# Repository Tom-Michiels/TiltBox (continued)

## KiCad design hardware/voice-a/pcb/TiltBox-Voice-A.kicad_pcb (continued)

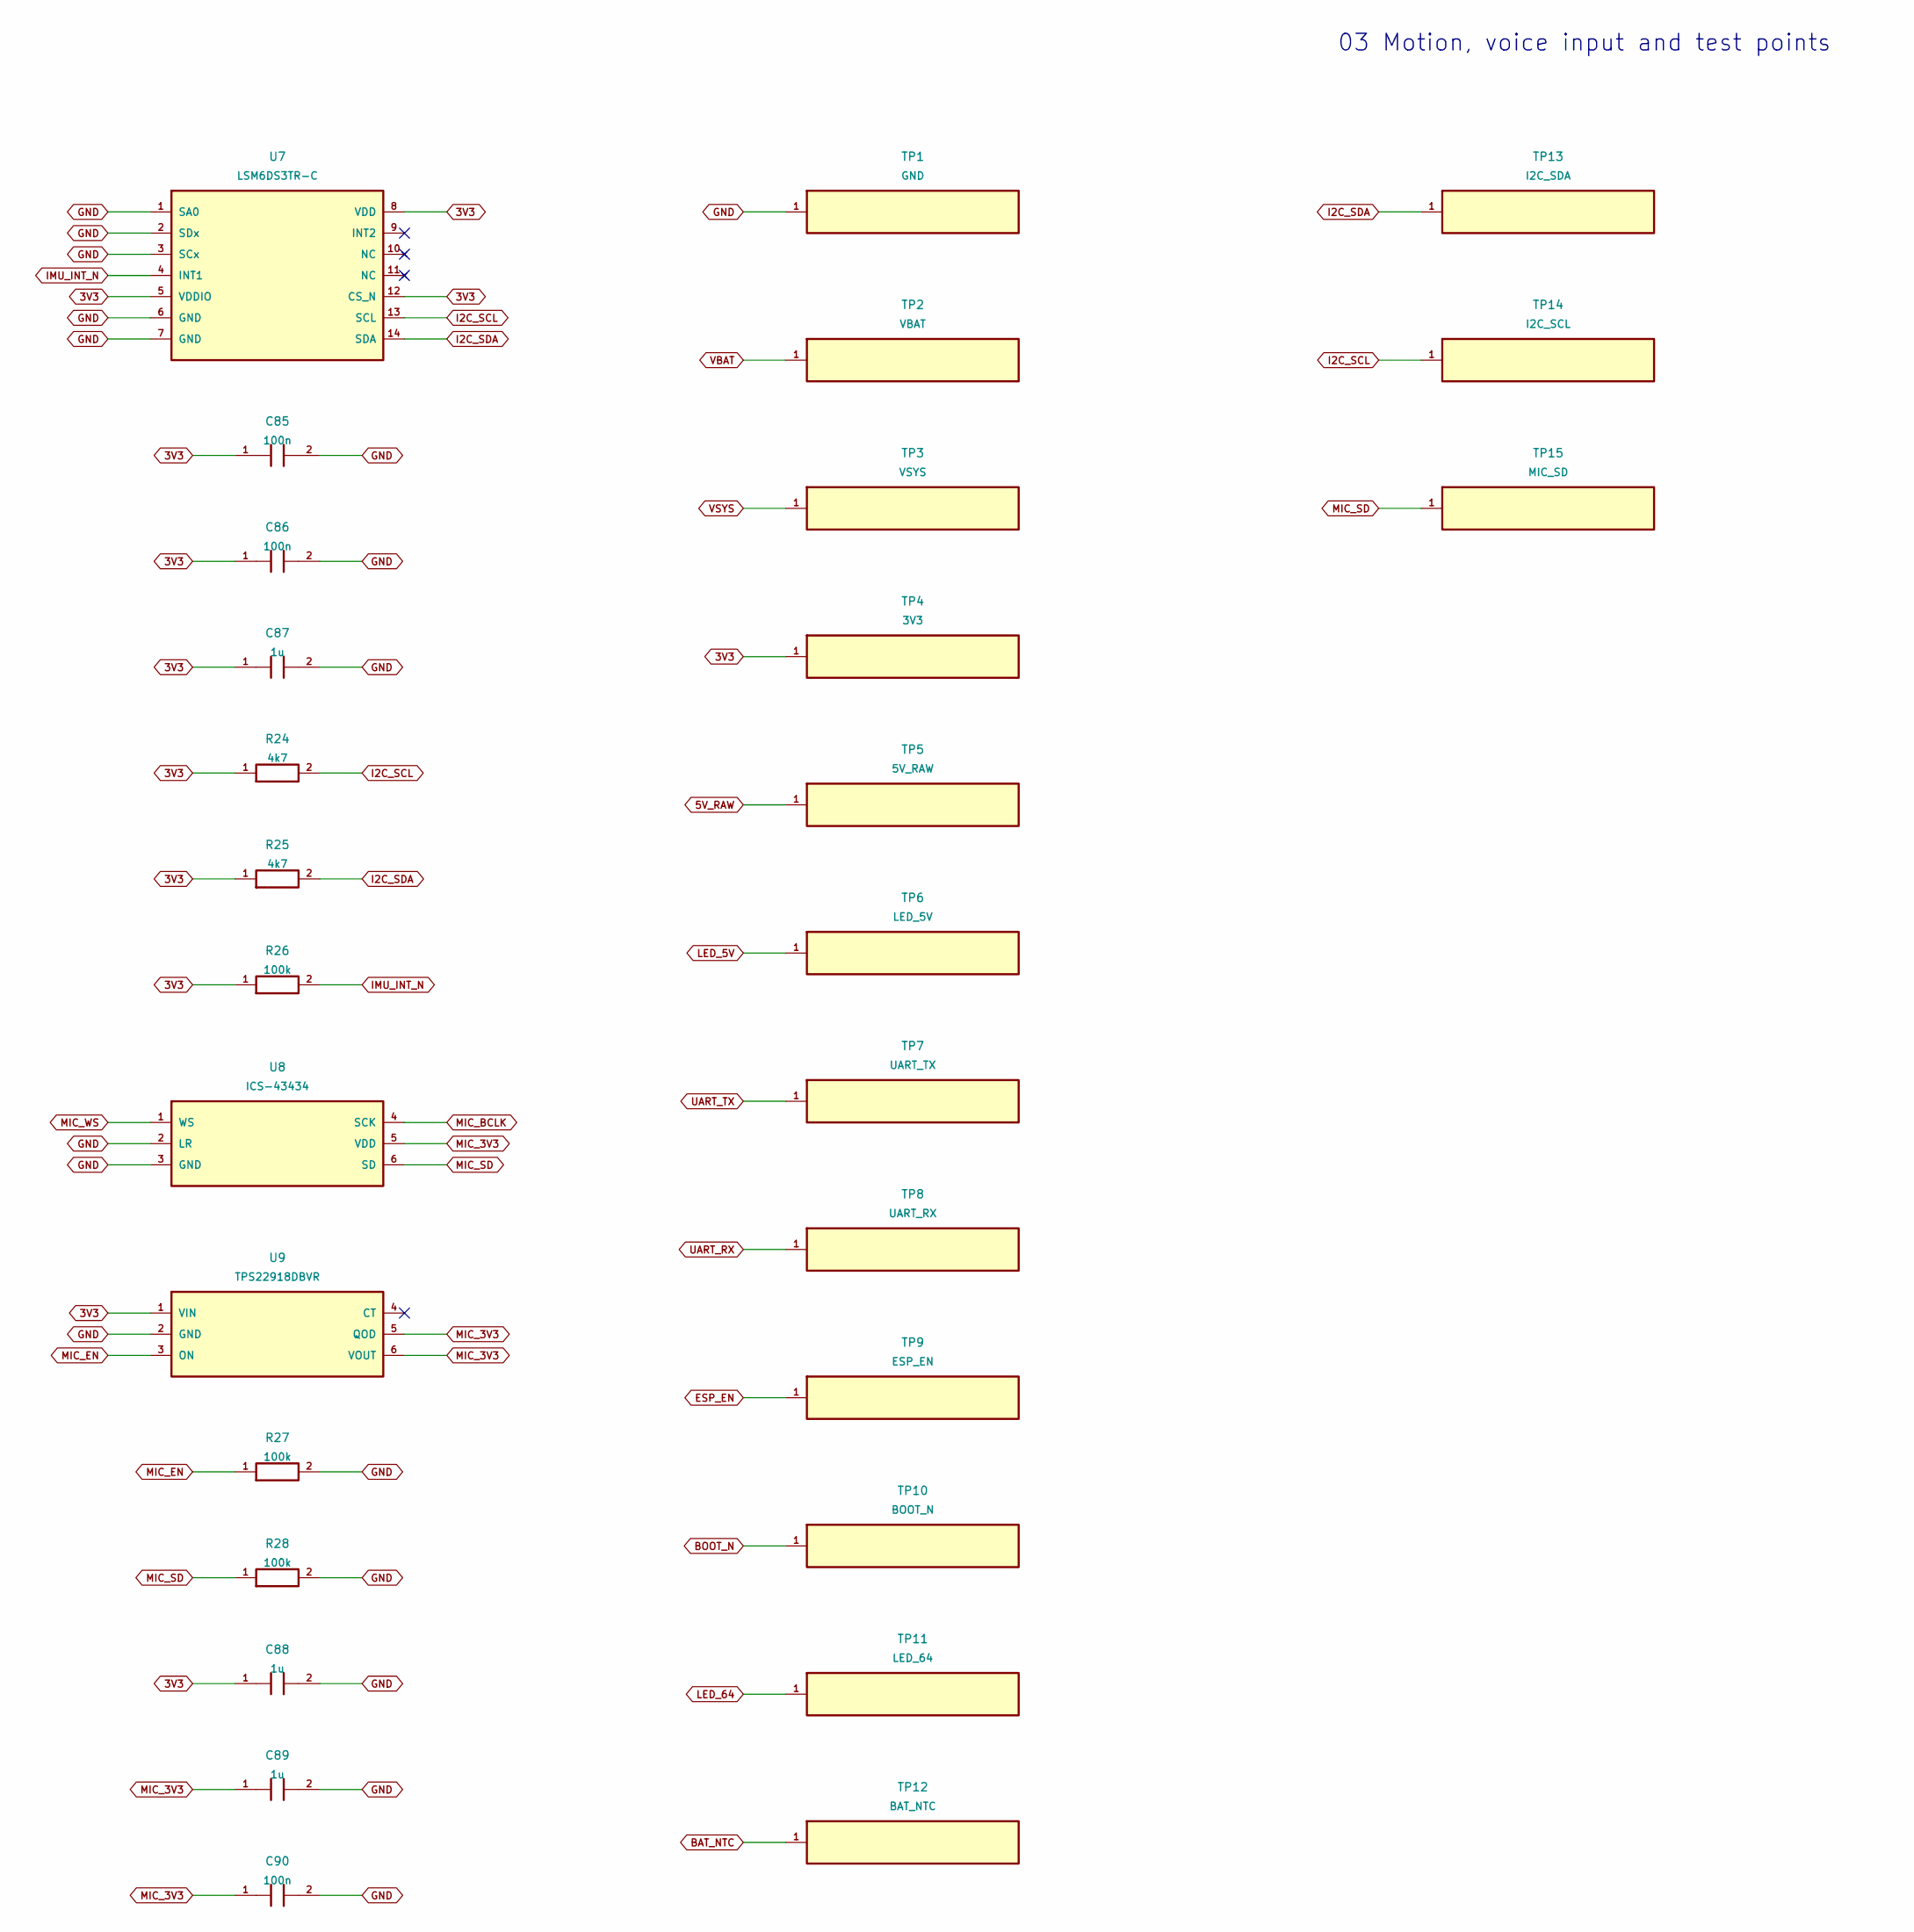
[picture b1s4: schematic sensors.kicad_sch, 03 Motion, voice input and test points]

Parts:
C85, C86, C90: 100n; C_0402_1005Metric; LCSC Part C1525
C87, C88, C89: 1u; C_0603_1608Metric; LCSC Part C15849
R24, R25: 4k7; R_0402_1005Metric; LCSC Part C25900
R26, R27, R28: 100k; R_0402_1005Metric; LCSC Part C25741
TP1: GND; TestPoint_Pad_D1.5mm
TP2: VBAT; TestPoint_Pad_D1.5mm
TP3: VSYS; TestPoint_Pad_D1.5mm
TP4: 3V3; TestPoint_Pad_D1.5mm
TP5: 5V_RAW; TestPoint_Pad_D1.5mm
TP6: LED_5V; TestPoint_Pad_D1.5mm
TP7: UART_TX; TestPoint_Pad_D1.5mm
TP8: UART_RX; TestPoint_Pad_D1.5mm
TP9: ESP_EN; TestPoint_Pad_D1.5mm
TP10: BOOT_N; TestPoint_Pad_D1.5mm
TP11: LED_64; TestPoint_Pad_D1.5mm
TP12: BAT_NTC; TestPoint_Pad_D1.5mm
TP13: I2C_SDA; TestPoint_Pad_D1.5mm
TP14: I2C_SCL; TestPoint_Pad_D1.5mm
TP15: MIC_SD; TestPoint_Pad_D1.5mm
U7: LSM6DS3TR-C; LGA-14_3x2.5mm_P0.5mm_LayoutBorder3x4y; LCSC Part C967633
U8: ICS-43434; InvenSense_ICS-43434-6_3.5x2.65mm; LCSC Part C5656610
U9: TPS22918DBVR; SOT-23-6; LCSC Part C131941

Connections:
3V3: C85.1, C86.1, C87.1, C88.1, R24.1, R25.1, R26.1, TP4.1, U7.5 (VDDIO), U7.8 (VDD), U7.12 (CS_N), U9.1 (VIN); also elsewhere on the board
5V_RAW: TP5.1; also elsewhere on the board
BAT_NTC: TP12.1; also elsewhere on the board
BOOT_N: TP10.1; also elsewhere on the board
ESP_EN: TP9.1; also elsewhere on the board
GND: C85.2, C86.2, C87.2, C88.2, C89.2, C90.2, R27.2, R28.2, TP1.1, U7.1 (SA0), U7.2 (SDx), U7.3 (SCx), U7.6 (GND), U7.7 (GND), U8.2 (LR), U8.3 (GND), U9.2 (GND); also elsewhere on the board
I2C_SCL: R24.2, TP14.1, U7.13 (SCL); also elsewhere on the board
I2C_SDA: R25.2, TP13.1, U7.14 (SDA); also elsewhere on the board
IMU_INT_N: R26.2, U7.4 (INT1); also elsewhere on the board
LED_5V: TP6.1; also elsewhere on the board
LED_64: TP11.1; also elsewhere on the board
MIC_3V3: C89.1, C90.1, U8.5 (VDD), U9.5 (QOD), U9.6 (VOUT)
MIC_BCLK: U8.4 (SCK); also elsewhere on the board
MIC_EN: R27.1, U9.3 (ON); also elsewhere on the board
MIC_SD: R28.1, TP15.1, U8.6 (SD); also elsewhere on the board
MIC_WS: U8.1 (WS); also elsewhere on the board
UART_RX: TP8.1; also elsewhere on the board
UART_TX: TP7.1; also elsewhere on the board
VBAT: TP2.1; also elsewhere on the board
VSYS: TP3.1; also elsewhere on the board

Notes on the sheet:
03 Motion, voice input and test points

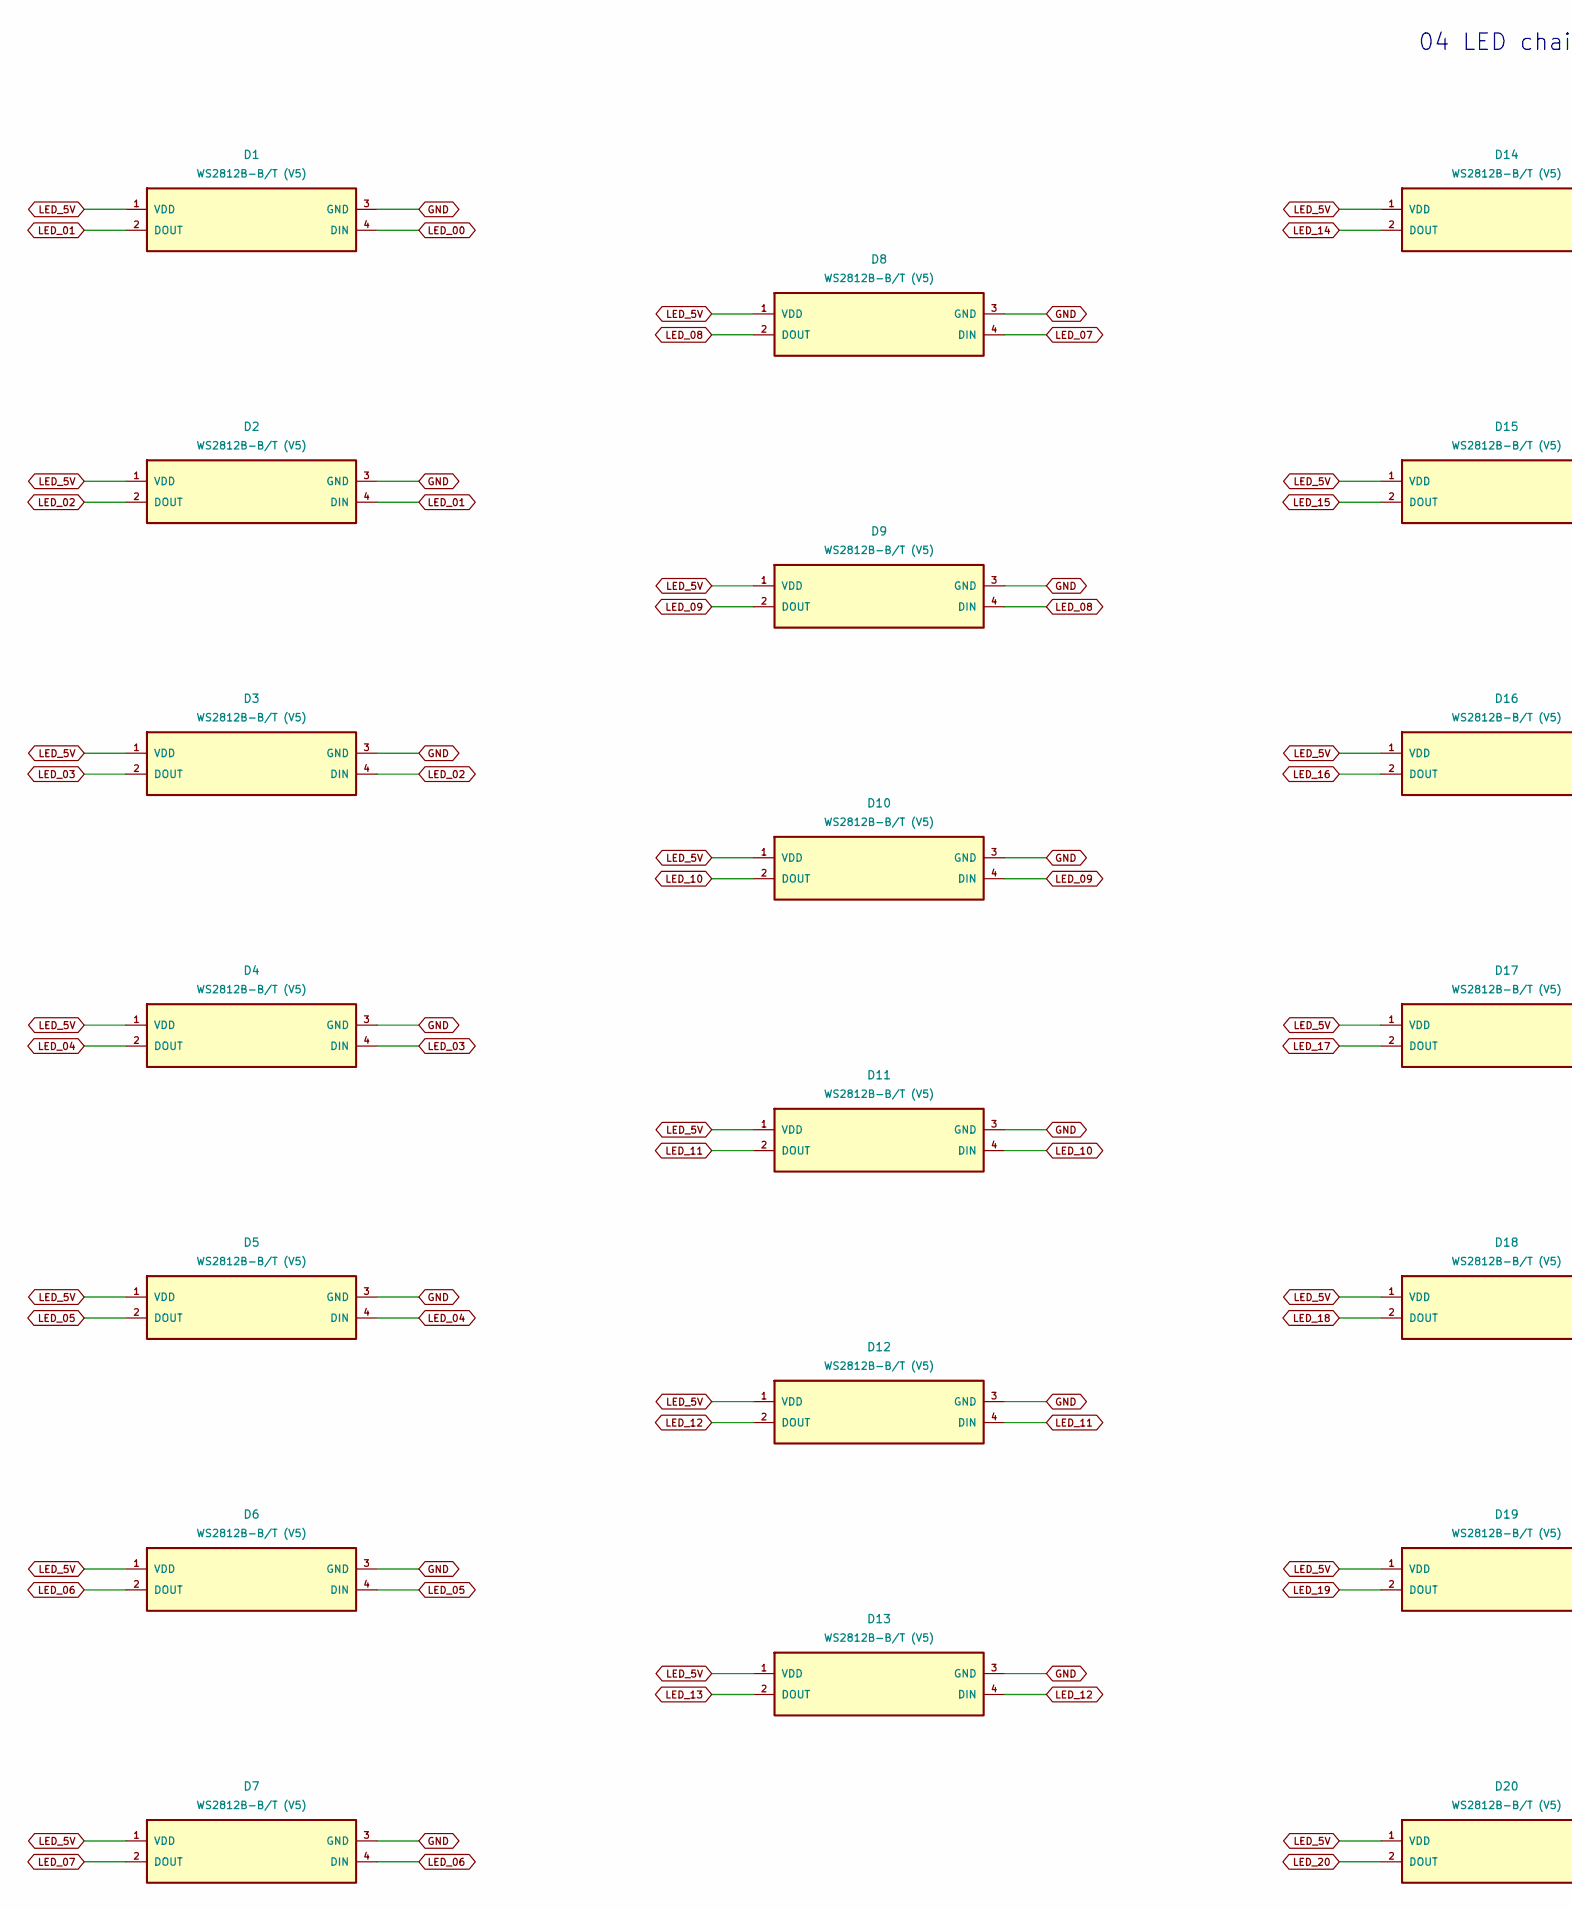
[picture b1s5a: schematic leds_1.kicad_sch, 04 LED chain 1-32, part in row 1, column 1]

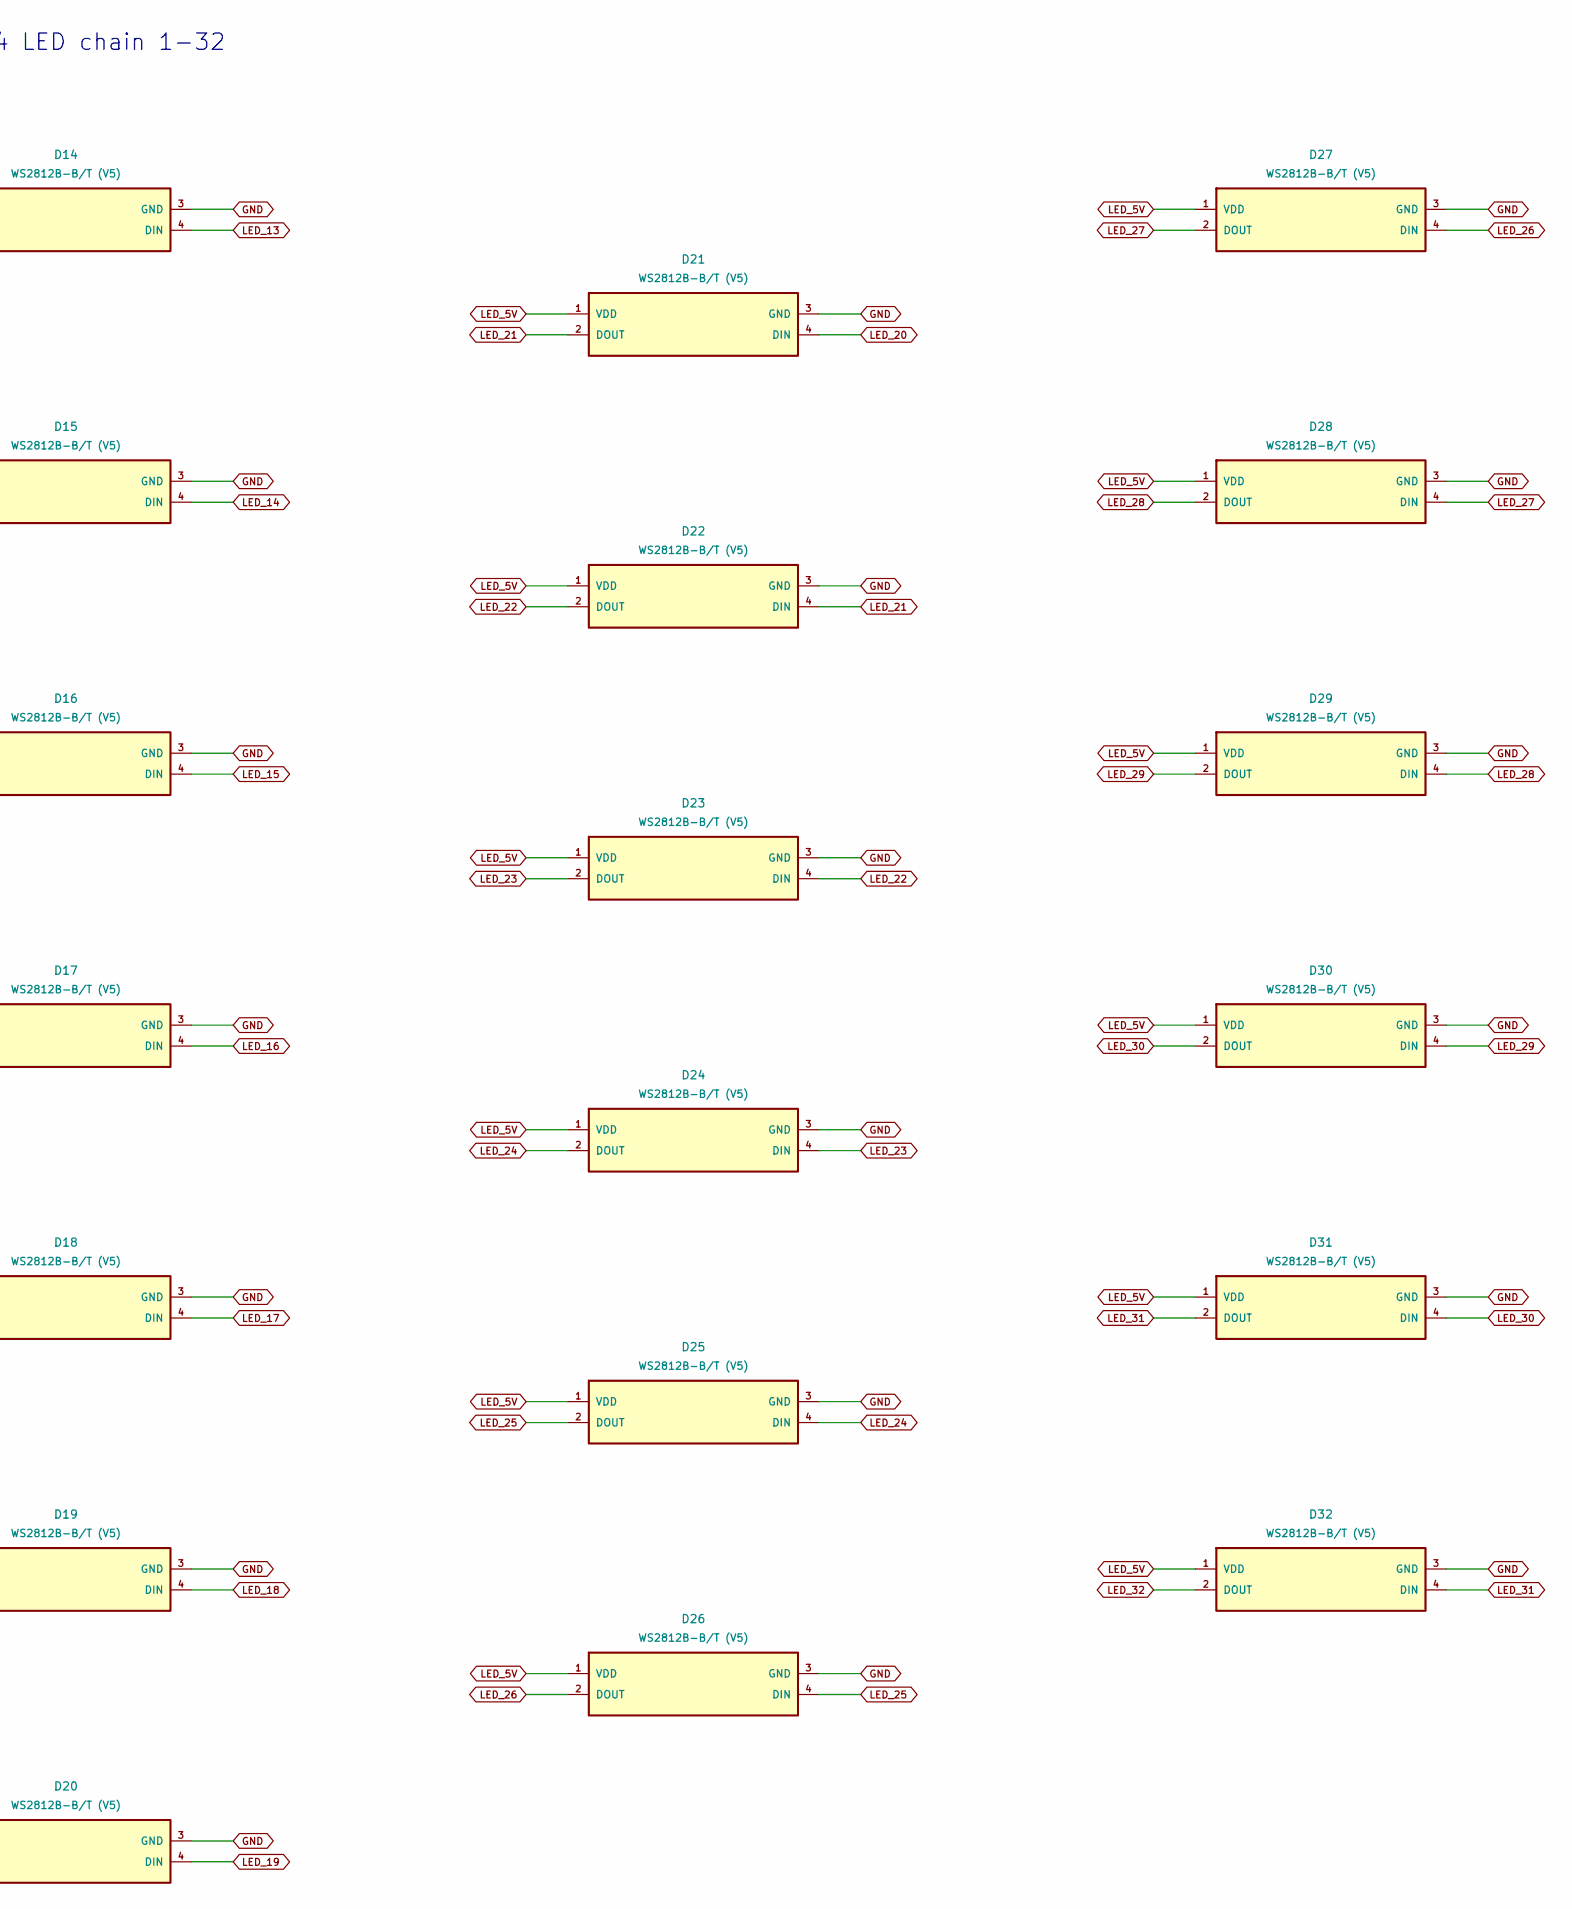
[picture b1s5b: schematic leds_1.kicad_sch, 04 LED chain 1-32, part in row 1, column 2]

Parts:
D1, D2, D3, D4, D5, D6, D7, D8, D9, D10, D11, D12, D13, D14, D15, D16, D17, D18, D19, D20, D21, D22, D23, D24, D25, D26, D27, D28, D29, D30, D31, D32: WS2812B-B/T (V5); LED_WS2812B_PLCC4_5.0x5.0mm_P3.2mm; LCSC Part C2761795

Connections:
GND: D1.3 (GND), D2.3 (GND), D3.3 (GND), D4.3 (GND), D5.3 (GND), D6.3 (GND), D7.3 (GND), D8.3 (GND), D9.3 (GND), D10.3 (GND), D11.3 (GND), D12.3 (GND), D13.3 (GND), D14.3 (GND), D15.3 (GND), D16.3 (GND), D17.3 (GND), D18.3 (GND), D19.3 (GND), D20.3 (GND), D21.3 (GND), D22.3 (GND), D23.3 (GND), D24.3 (GND), D25.3 (GND), D26.3 (GND), D27.3 (GND), D28.3 (GND), D29.3 (GND), D30.3 (GND), D31.3 (GND), D32.3 (GND); also elsewhere on the board
LED_00: D1.4 (DIN); also elsewhere on the board
LED_01: D1.2 (DOUT), D2.4 (DIN)
LED_02: D2.2 (DOUT), D3.4 (DIN)
LED_03: D3.2 (DOUT), D4.4 (DIN)
LED_04: D4.2 (DOUT), D5.4 (DIN)
LED_05: D5.2 (DOUT), D6.4 (DIN)
LED_5V: D1.1 (VDD), D2.1 (VDD), D3.1 (VDD), D4.1 (VDD), D5.1 (VDD), D6.1 (VDD), D7.1 (VDD), D8.1 (VDD), D9.1 (VDD), D10.1 (VDD), D11.1 (VDD), D12.1 (VDD), D13.1 (VDD), D14.1 (VDD), D15.1 (VDD), D16.1 (VDD), D17.1 (VDD), D18.1 (VDD), D19.1 (VDD), D20.1 (VDD), D21.1 (VDD), D22.1 (VDD), D23.1 (VDD), D24.1 (VDD), D25.1 (VDD), D26.1 (VDD), D27.1 (VDD), D28.1 (VDD), D29.1 (VDD), D30.1 (VDD), D31.1 (VDD), D32.1 (VDD); also elsewhere on the board
LED_06: D6.2 (DOUT), D7.4 (DIN)
LED_07: D7.2 (DOUT), D8.4 (DIN)
LED_08: D8.2 (DOUT), D9.4 (DIN)
LED_09: D9.2 (DOUT), D10.4 (DIN)
LED_10: D10.2 (DOUT), D11.4 (DIN)
LED_11: D11.2 (DOUT), D12.4 (DIN)
LED_12: D12.2 (DOUT), D13.4 (DIN)
LED_13: D13.2 (DOUT), D14.4 (DIN)
LED_14: D14.2 (DOUT), D15.4 (DIN)
LED_15: D15.2 (DOUT), D16.4 (DIN)
LED_16: D16.2 (DOUT), D17.4 (DIN)
LED_17: D17.2 (DOUT), D18.4 (DIN)
LED_18: D18.2 (DOUT), D19.4 (DIN)
LED_19: D19.2 (DOUT), D20.4 (DIN)
LED_20: D20.2 (DOUT), D21.4 (DIN)
LED_21: D21.2 (DOUT), D22.4 (DIN)
LED_22: D22.2 (DOUT), D23.4 (DIN)
LED_23: D23.2 (DOUT), D24.4 (DIN)
LED_24: D24.2 (DOUT), D25.4 (DIN)
LED_25: D25.2 (DOUT), D26.4 (DIN)
LED_26: D26.2 (DOUT), D27.4 (DIN)
LED_27: D27.2 (DOUT), D28.4 (DIN)
LED_28: D28.2 (DOUT), D29.4 (DIN)
LED_29: D29.2 (DOUT), D30.4 (DIN)
LED_30: D30.2 (DOUT), D31.4 (DIN)
LED_31: D31.2 (DOUT), D32.4 (DIN)
LED_32: D32.2 (DOUT); also elsewhere on the board

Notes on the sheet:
04 LED chain 1-32

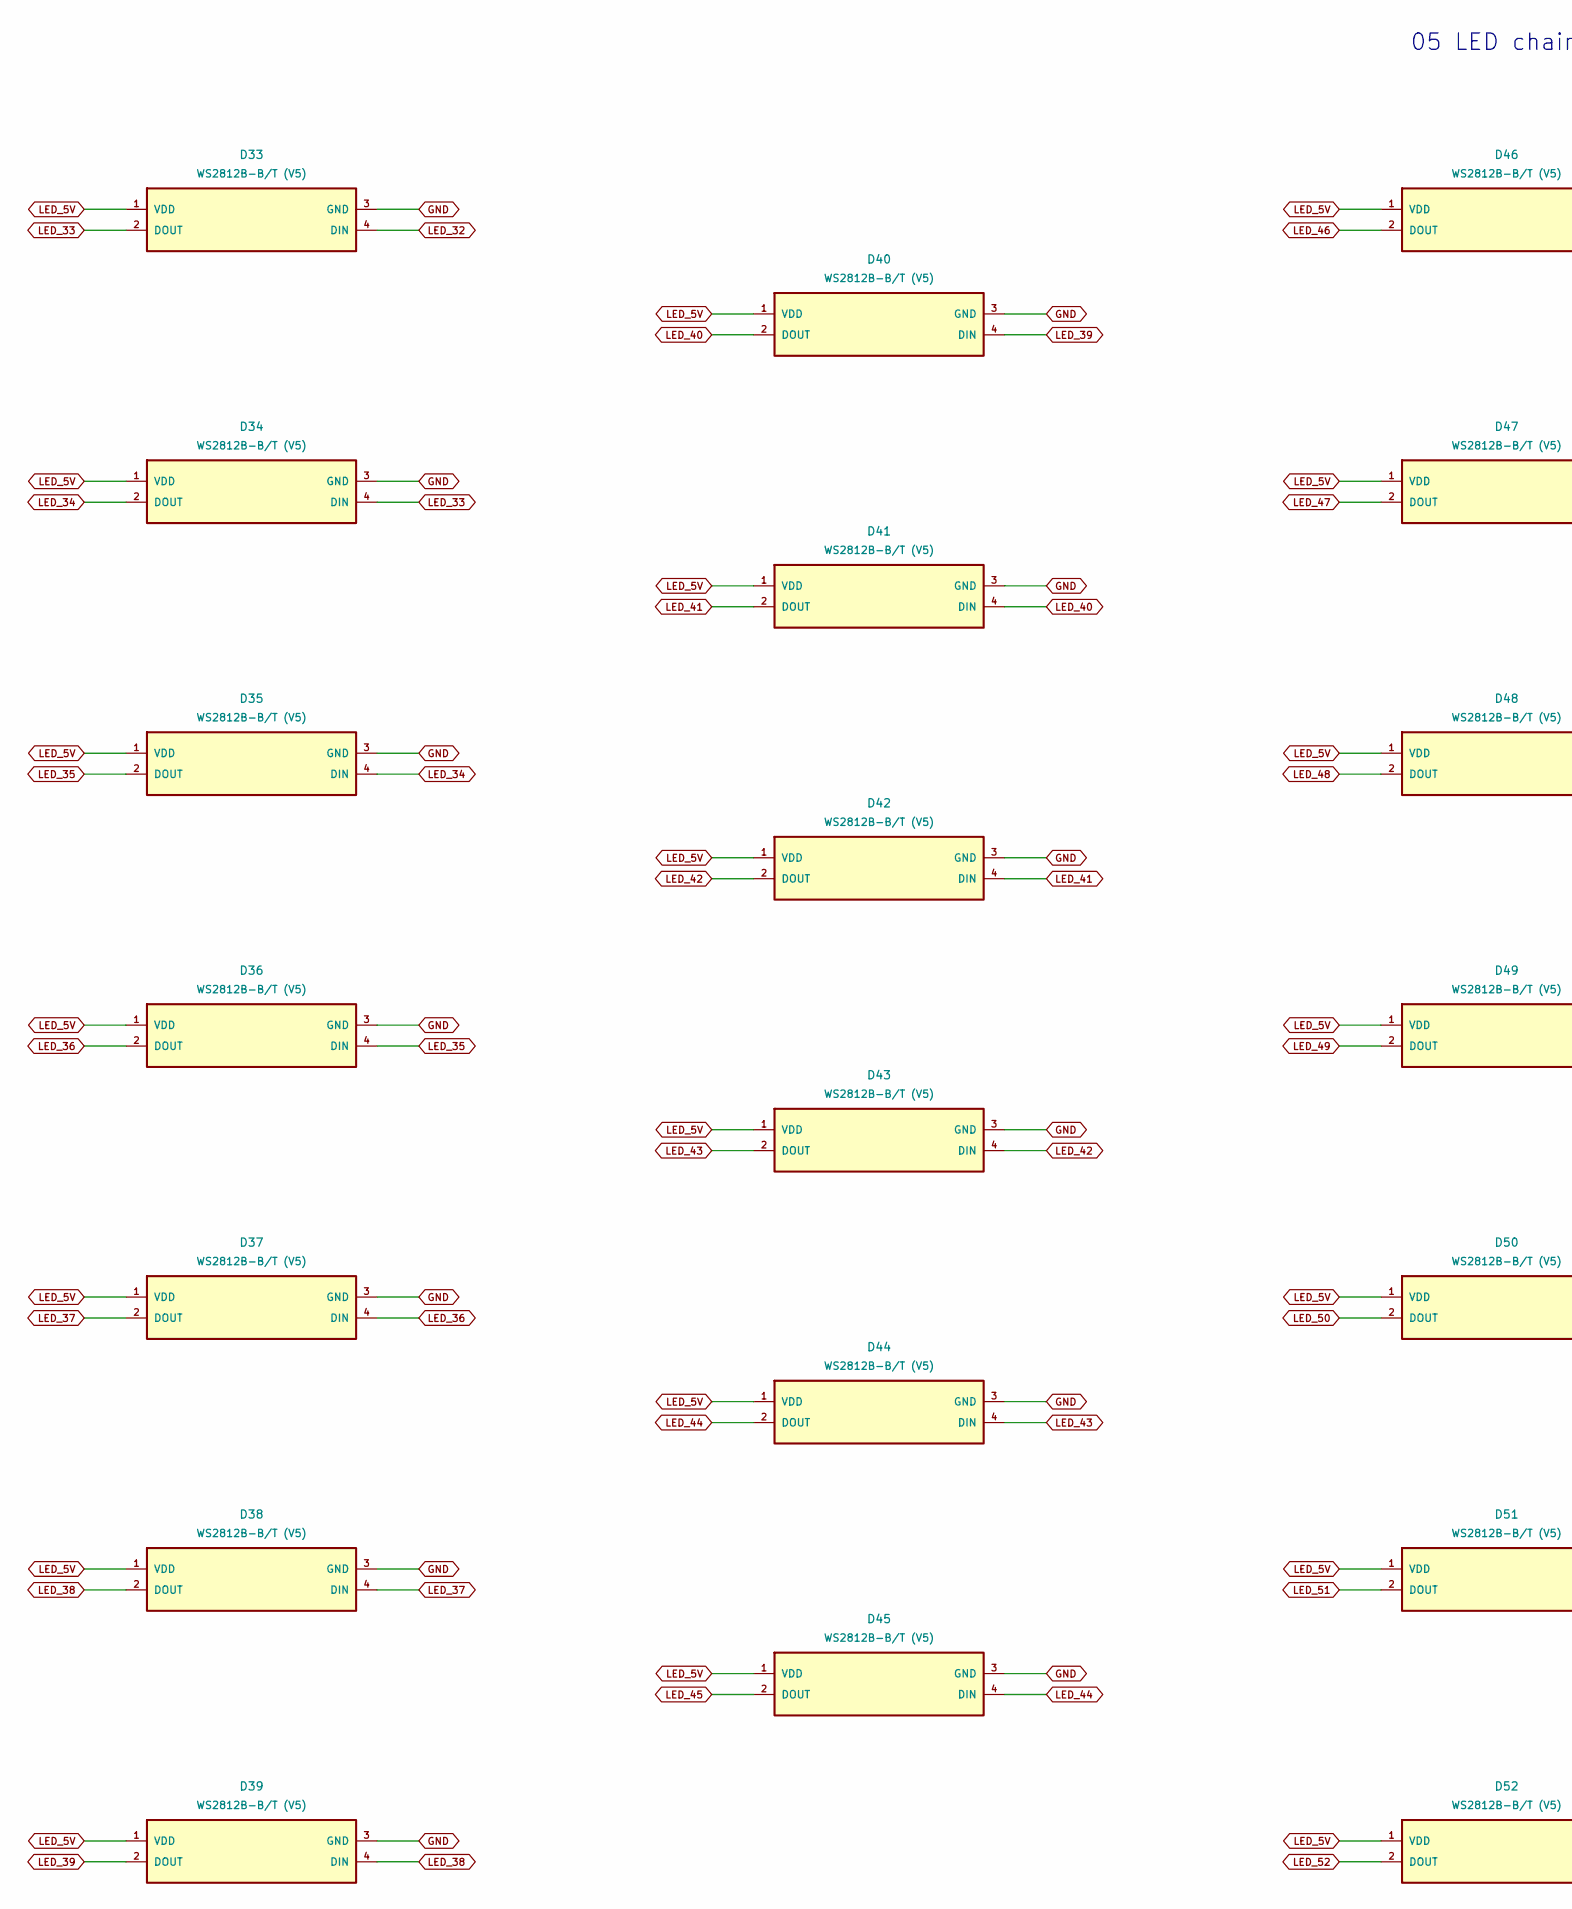
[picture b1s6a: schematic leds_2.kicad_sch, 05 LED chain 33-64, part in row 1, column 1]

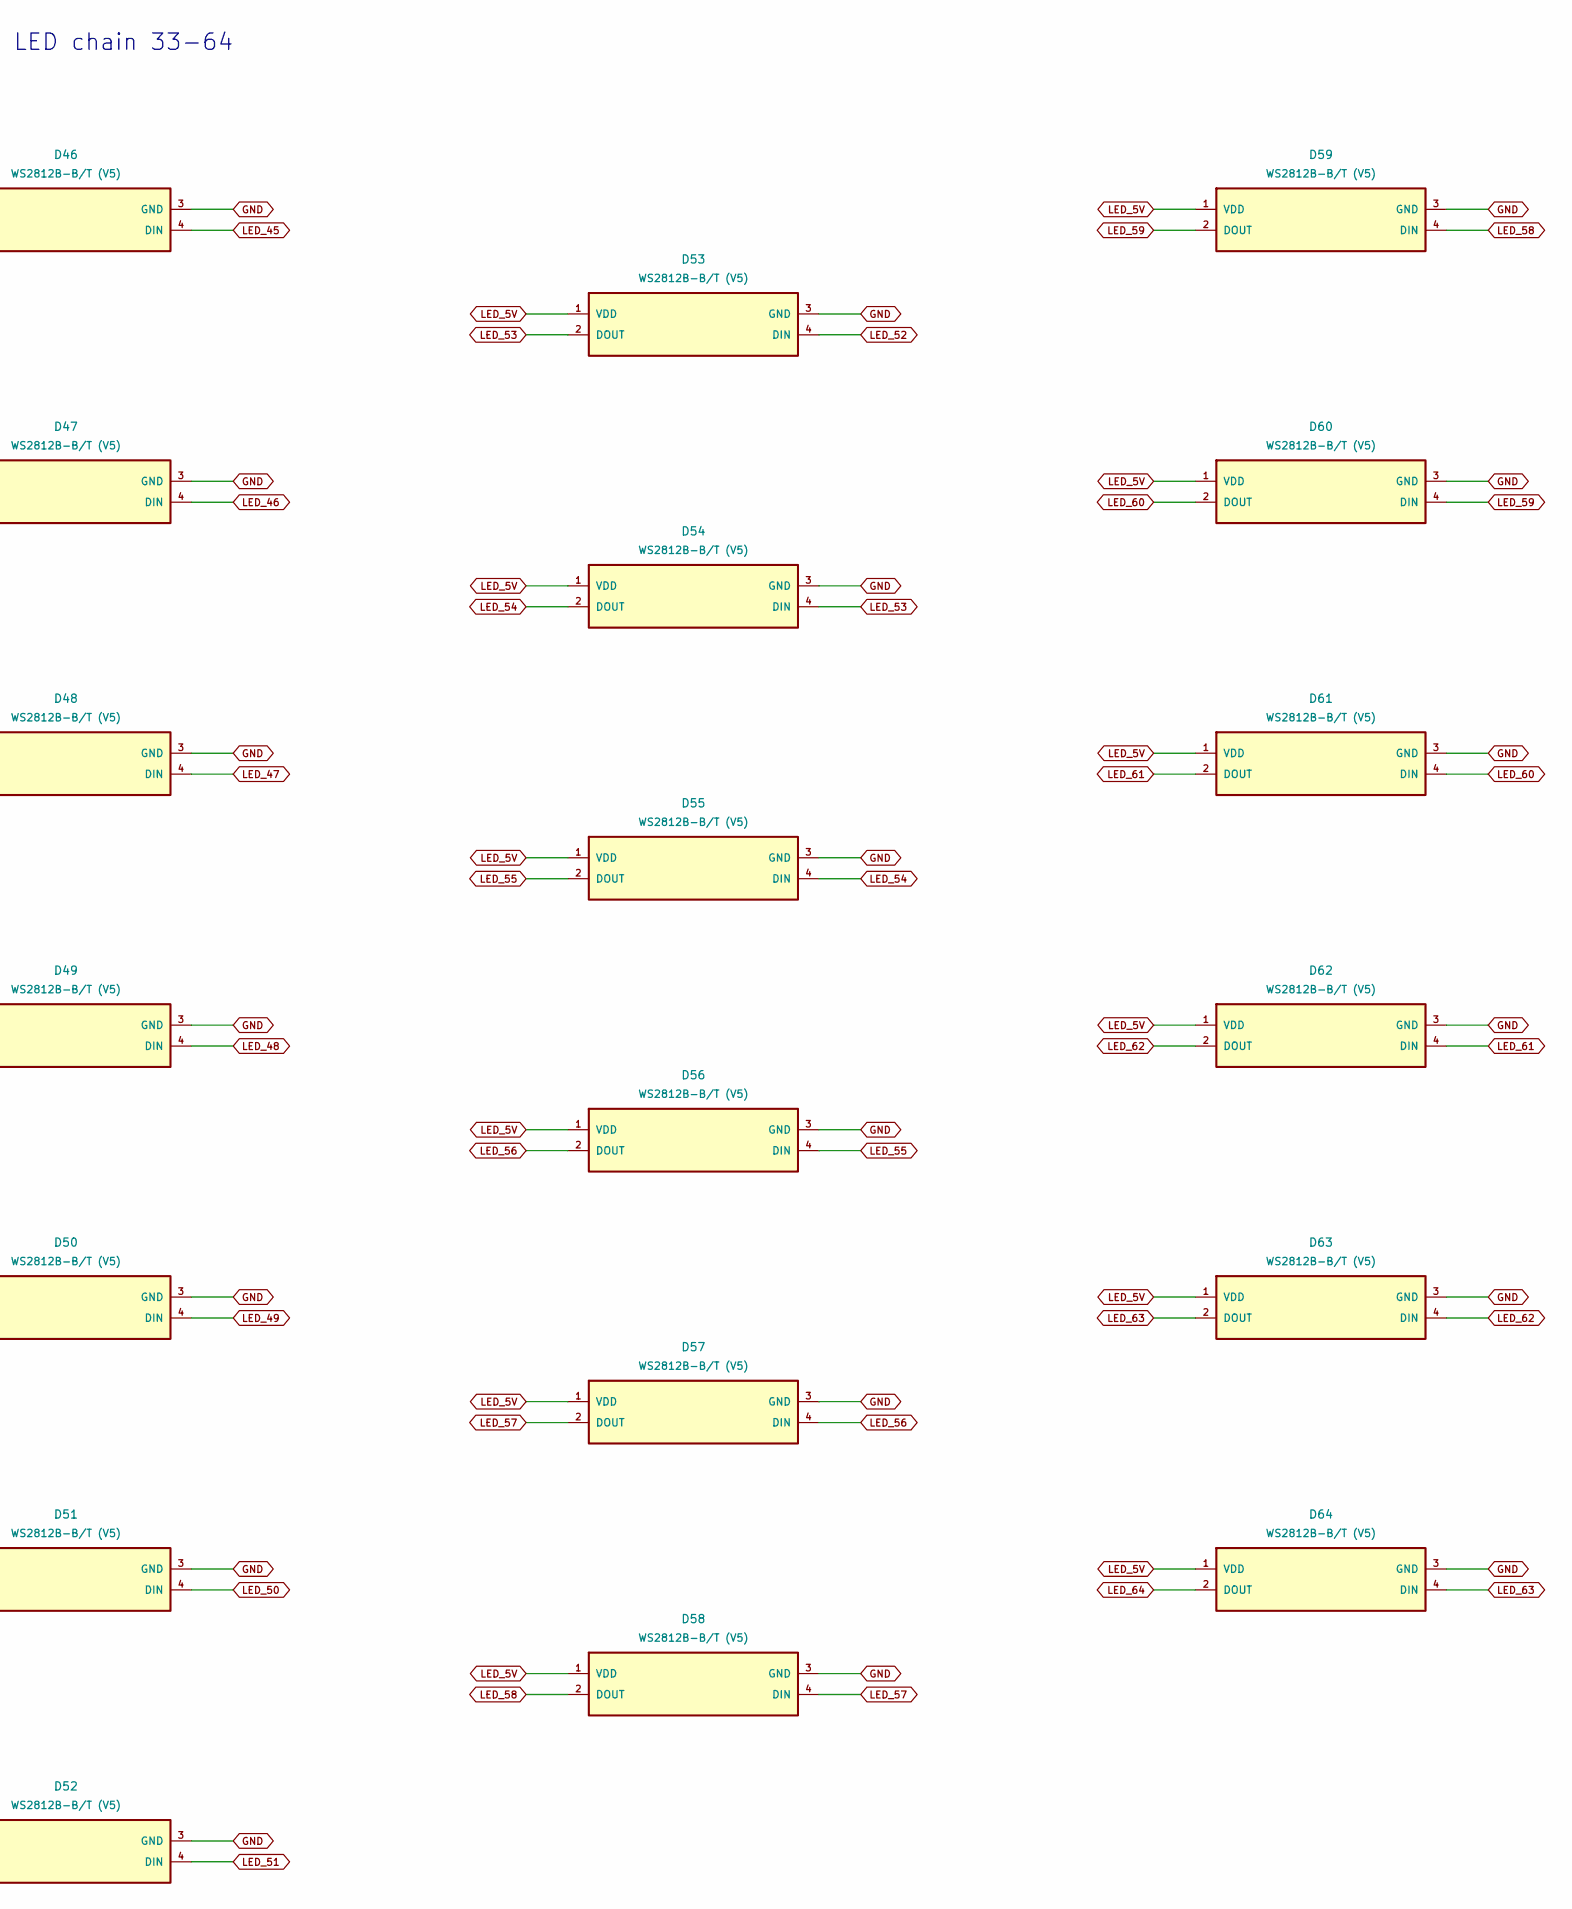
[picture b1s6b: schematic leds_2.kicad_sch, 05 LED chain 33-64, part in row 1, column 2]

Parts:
D33, D34, D35, D36, D37, D38, D39, D40, D41, D42, D43, D44, D45, D46, D47, D48, D49, D50, D51, D52, D53, D54, D55, D56, D57, D58, D59, D60, D61, D62, D63, D64: WS2812B-B/T (V5); LED_WS2812B_PLCC4_5.0x5.0mm_P3.2mm; LCSC Part C2761795

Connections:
GND: D33.3 (GND), D34.3 (GND), D35.3 (GND), D36.3 (GND), D37.3 (GND), D38.3 (GND), D39.3 (GND), D40.3 (GND), D41.3 (GND), D42.3 (GND), D43.3 (GND), D44.3 (GND), D45.3 (GND), D46.3 (GND), D47.3 (GND), D48.3 (GND), D49.3 (GND), D50.3 (GND), D51.3 (GND), D52.3 (GND), D53.3 (GND), D54.3 (GND), D55.3 (GND), D56.3 (GND), D57.3 (GND), D58.3 (GND), D59.3 (GND), D60.3 (GND), D61.3 (GND), D62.3 (GND), D63.3 (GND), D64.3 (GND); also elsewhere on the board
LED_5V: D33.1 (VDD), D34.1 (VDD), D35.1 (VDD), D36.1 (VDD), D37.1 (VDD), D38.1 (VDD), D39.1 (VDD), D40.1 (VDD), D41.1 (VDD), D42.1 (VDD), D43.1 (VDD), D44.1 (VDD), D45.1 (VDD), D46.1 (VDD), D47.1 (VDD), D48.1 (VDD), D49.1 (VDD), D50.1 (VDD), D51.1 (VDD), D52.1 (VDD), D53.1 (VDD), D54.1 (VDD), D55.1 (VDD), D56.1 (VDD), D57.1 (VDD), D58.1 (VDD), D59.1 (VDD), D60.1 (VDD), D61.1 (VDD), D62.1 (VDD), D63.1 (VDD), D64.1 (VDD); also elsewhere on the board
LED_32: D33.4 (DIN); also elsewhere on the board
LED_33: D33.2 (DOUT), D34.4 (DIN)
LED_34: D34.2 (DOUT), D35.4 (DIN)
LED_35: D35.2 (DOUT), D36.4 (DIN)
LED_36: D36.2 (DOUT), D37.4 (DIN)
LED_37: D37.2 (DOUT), D38.4 (DIN)
LED_38: D38.2 (DOUT), D39.4 (DIN)
LED_39: D39.2 (DOUT), D40.4 (DIN)
LED_40: D40.2 (DOUT), D41.4 (DIN)
LED_41: D41.2 (DOUT), D42.4 (DIN)
LED_42: D42.2 (DOUT), D43.4 (DIN)
LED_43: D43.2 (DOUT), D44.4 (DIN)
LED_44: D44.2 (DOUT), D45.4 (DIN)
LED_45: D45.2 (DOUT), D46.4 (DIN)
LED_46: D46.2 (DOUT), D47.4 (DIN)
LED_47: D47.2 (DOUT), D48.4 (DIN)
LED_48: D48.2 (DOUT), D49.4 (DIN)
LED_49: D49.2 (DOUT), D50.4 (DIN)
LED_50: D50.2 (DOUT), D51.4 (DIN)
LED_51: D51.2 (DOUT), D52.4 (DIN)
LED_52: D52.2 (DOUT), D53.4 (DIN)
LED_53: D53.2 (DOUT), D54.4 (DIN)
LED_54: D54.2 (DOUT), D55.4 (DIN)
LED_55: D55.2 (DOUT), D56.4 (DIN)
LED_56: D56.2 (DOUT), D57.4 (DIN)
LED_57: D57.2 (DOUT), D58.4 (DIN)
LED_58: D58.2 (DOUT), D59.4 (DIN)
LED_59: D59.2 (DOUT), D60.4 (DIN)
LED_60: D60.2 (DOUT), D61.4 (DIN)
LED_61: D61.2 (DOUT), D62.4 (DIN)
LED_62: D62.2 (DOUT), D63.4 (DIN)
LED_63: D63.2 (DOUT), D64.4 (DIN)
LED_64: D64.2 (DOUT); also elsewhere on the board

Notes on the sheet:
05 LED chain 33-64
